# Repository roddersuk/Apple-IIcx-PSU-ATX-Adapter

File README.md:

# Apple-IIcx-PSU-ATX-Adapter
Apple Mac IIcx PSU ATX Adapter

The PSU in these old computers suffer with age, particularly the Rifa capacitors which have a tendency to explode.
The general consensus seems to be that it isn't worth trying to repair them as this is likely to only extend their life by a few years.
I therefore decided to replace the guts of the PSU with a mini ATX PSU but there are a couple of issues with hooking it up:
1) The Apple PSU has a special connector to the logic board allowing the PSU to be plugged in as a unit.
2) The ATX PSU does not have direct provision for the soft start capability.
3) Many ATX units don't have a monitor A/C pass-through

I decided to design this PCB to solve all of these issues. It is designed to connect to the power plug from the mains input unit, pass AC power 
to the ATX board, get DC power back via the ATX connector and use the logic board plug and wires from the old PSU.

The ATX PSU I have used is from FSP Group Inc. Model FSP270-60LE as this has comparable power output capabilities.

I have also designed a mounting plate for the ATX PCB which can be 3D printed.

See files in Docs for the schematic and details of the build.

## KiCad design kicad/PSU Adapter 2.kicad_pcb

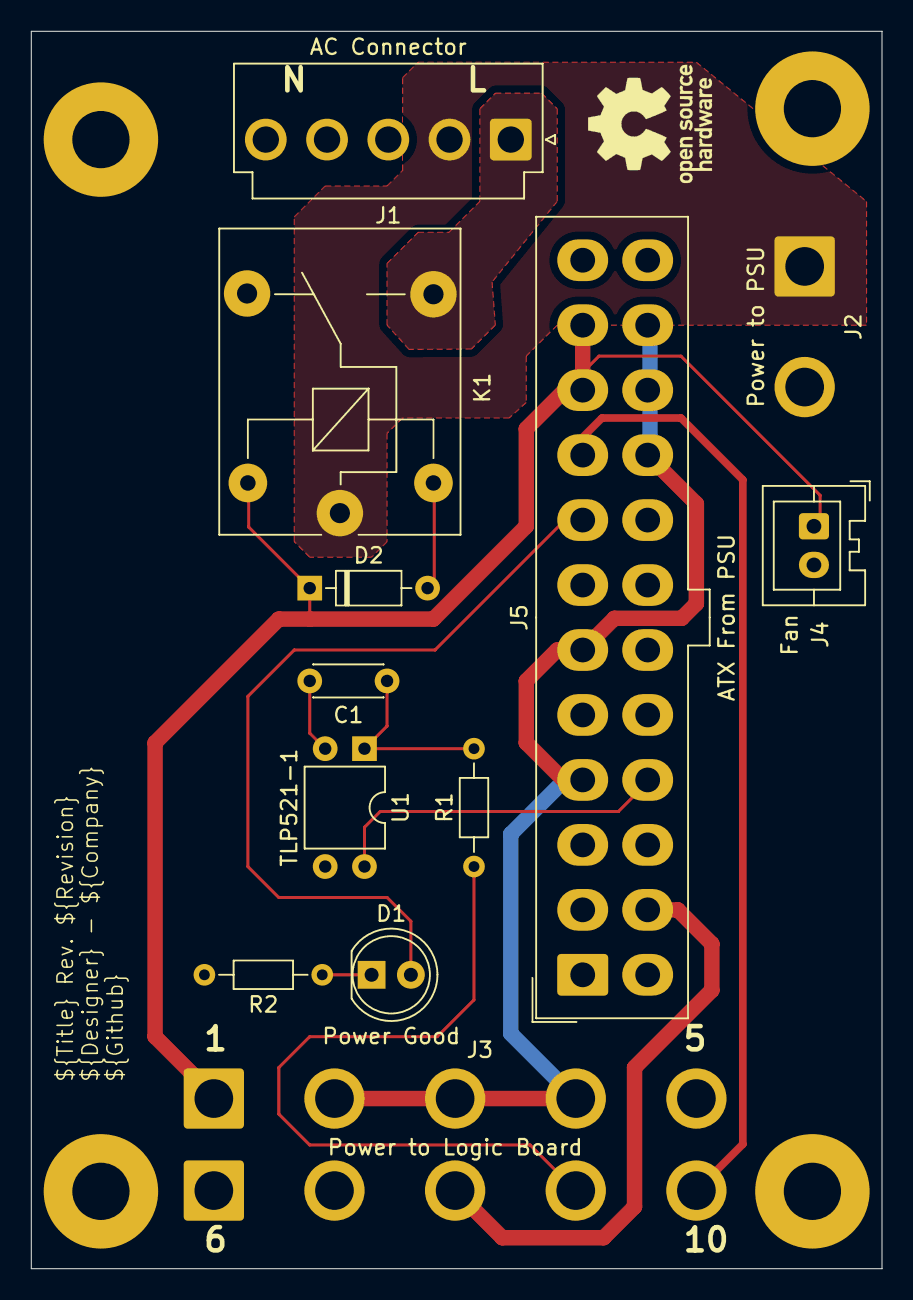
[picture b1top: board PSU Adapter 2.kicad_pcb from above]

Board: 2 copper layers, 55.0 x 80.0 mm, 17 parts (0 on the bottom side), 13 nets.

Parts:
C1: 0.1uF; C_Disc_D4.3mm_W1.9mm_P5.00mm
D1: Power Good; LED_D5.0mm
D2: 1N4148; D_DO-35_SOD27_P7.62mm_Horizontal
H1, H2, H3, H4: MountingHole_Pad; MountingHole_3.7mm_Pad
J1: AC Connector; JST_VH_B5P-VH-B_1x05_P3.96mm_Vertical
J2: Power to PSU; SolderWire-2sqmm_1x02_P7.8mm_D2mm_OD3.9mm
J3: Power to Logic Board; SolderWire-2sqmm_1x05_P7.8mm_D2mm_OD3.9mm
J4: Fan; JST_XA_B02B-XASK-1_1x02_P2.50mm_Vertical
J5: ATX From PSU; Molex_Mini-Fit_Jr_5566-24A_2x12_P4.20mm_Vertical_Chinese
J6: Conn_01x05_Pin; SolderWire-2sqmm_1x05_P7.8mm_D2mm_OD3.9mm
K1: AC Passthrough Relay; Relay_SPDT_SANYOU_SRD_Series_Form_C
R1, R2: 1k; R_Axial_DIN0204_L3.6mm_D1.6mm_P7.62mm_Horizontal
U1: TLP521-1; DIP-4_W7.62mm

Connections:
/+5V: J3.2, J3.3, J3.4, J5.4 (+5V), J5.6 (+5V), J5.21 (+5V), J5.22 (+5V), J5.23 (+5V)
/+5VSB: J5.9 (+5VSB), J6.5
/+12V: D2.1 (K), J3.1, J4.1, J5.10 (+12V), J5.11 (+12V), K1.5
/-12V: J5.14 (-12V), J6.3
/AC -ve: J1.4, J1.5, J2.2
/AC Input +ve: J1.2, J2.1, K1.1
/AC Ouput +ve: J1.1, K1.3
/GND: C1.2, D2.2 (A), J3.5, J4.2, J5.3 (GND), J5.5 (GND), J5.7 (GND), J5.15 (GND), J5.17 (GND), J5.18 (GND), J5.19 (GND), J5.24 (GND), J6.1, J6.2, K1.2, R2.2, U1.2, U1.3
/PFW: J6.4, R1.1
/PS_ON: J5.16 (PS_ON#), U1.4
/PWR_OK: D1.2 (A), J5.8 (PWR_OK)
unnamed: C1.1, R1.2, U1.1
unnamed: D1.1 (K), R2.1

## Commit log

2024-11-26 Add files via upload
    Updated to rev 0.3
2024-11-26 Add files via upload
    Updated to rev 0.3 including footprint for Chinese ATX connector which has 4.2mm pitch between rows (Molex spec is 5.5mm)
2024-12-17 Add files via upload
    Increased hole size
2024-12-17 Add files via upload
    Modified ATX connector
2024-12-17 Add files via upload
    Adapter plate to fit ATX PSU in Apple PSU case.
2024-12-18 Add files via upload
    Fix soft start
2024-12-18 Add files via upload
    Fix to Soft Start
